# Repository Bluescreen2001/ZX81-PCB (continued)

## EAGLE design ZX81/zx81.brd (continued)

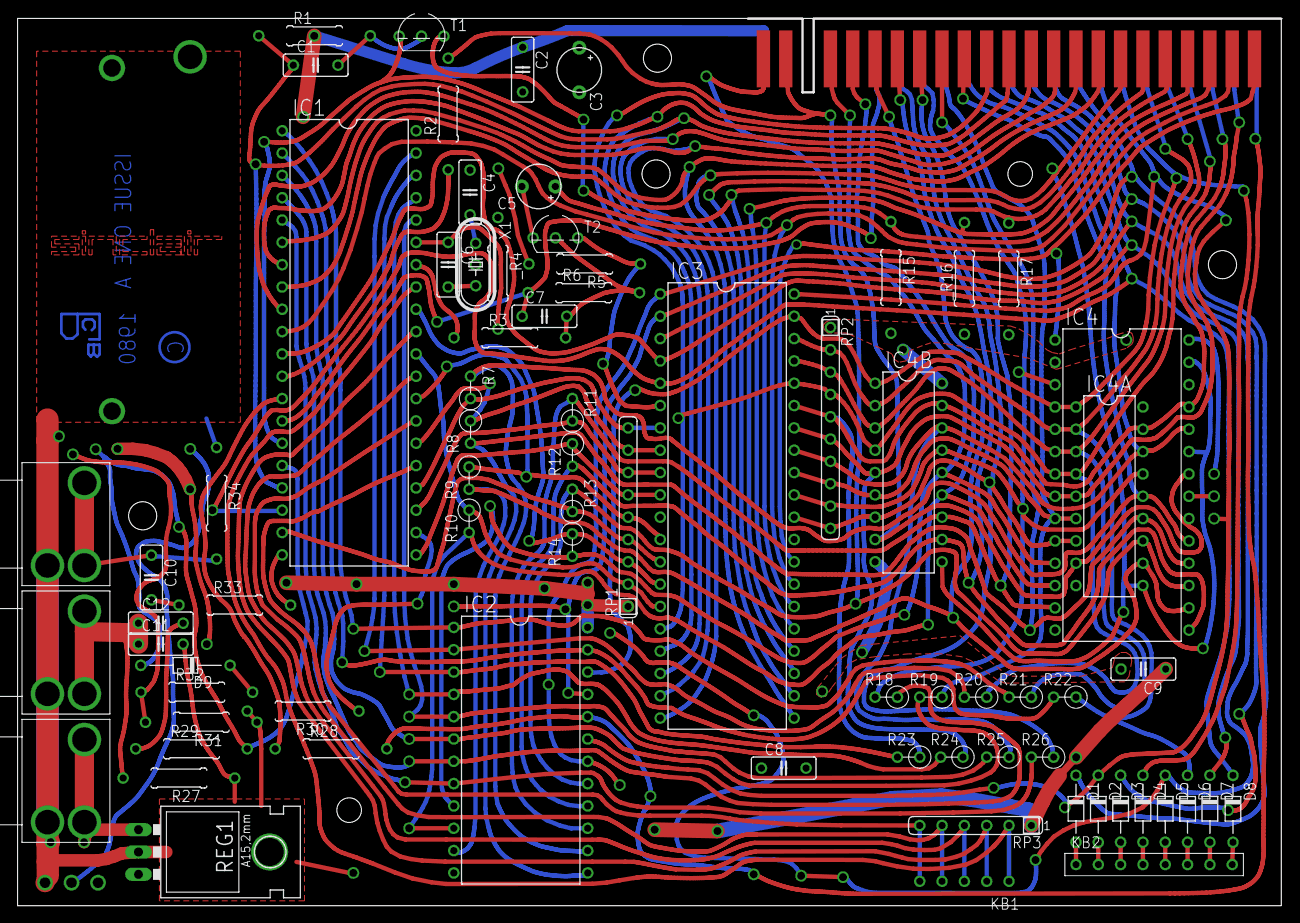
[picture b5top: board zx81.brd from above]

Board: 2 copper layers, 143.7 x 100.8 mm, 74 parts (0 on the bottom side), 88 nets.

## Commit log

2023-04-12 Add files via upload
    Changed connectors to 4 pin version. Corrected Issue 3 C string and added a year
